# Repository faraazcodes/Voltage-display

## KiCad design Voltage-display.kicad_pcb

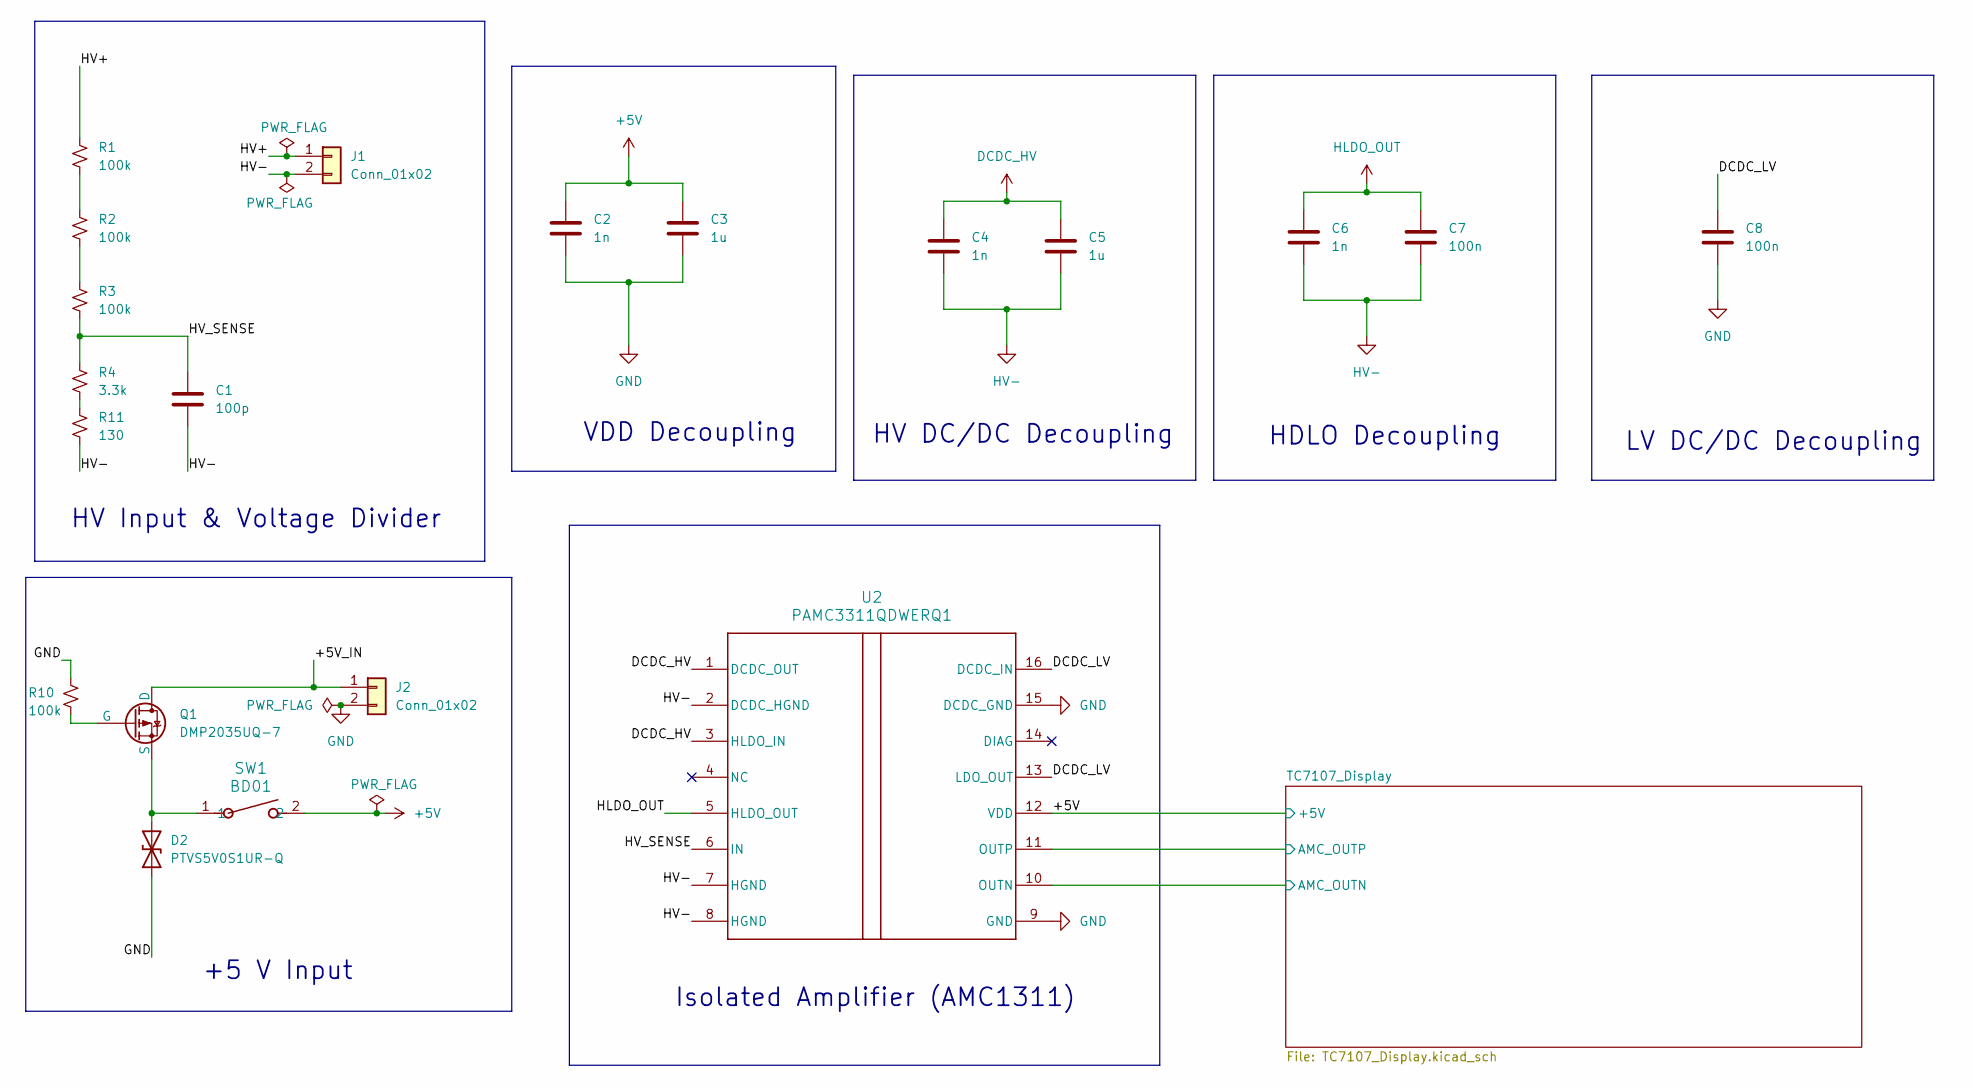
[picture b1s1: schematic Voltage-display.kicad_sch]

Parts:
C1: 100p; C_0805_2012Metric_Pad1.18x1.45mm_HandSolder
C2, C4, C6: 1n; C_0805_2012Metric_Pad1.18x1.45mm_HandSolder
C3, C5: 1u; C_1206_3216Metric_Pad1.33x1.80mm_HandSolder
C7, C8: 100n; C_1206_3216Metric_Pad1.33x1.80mm_HandSolder
D2: PTVS5V0S1UR-Q; SOD123W
J1, J2: Conn_01x02; PinHeader_1x02_P2.54mm_Vertical
Q1: DMP2035UQ-7; SOT96P240X115-3N
R1, R2, R3, R10: 100k; R_1206_3216Metric_Pad1.30x1.75mm_HandSolder
R4: 3.3k; R_1206_3216Metric_Pad1.30x1.75mm_HandSolder
R11: 130; R_1206_3216Metric_Pad1.30x1.75mm_HandSolder
SW1: BD01; SW_BD01_CNK
U2: PAMC3311QDWERQ1; DWE0016A-IPC_A

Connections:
+5V: C2.1, C3.1, SW1.2, U2.12 (VDD); also elsewhere on the board
/+5V_IN: J2.1, Q1.1 (D)
/DCDC_LV: C8.1, U2.13 (LDO_OUT), U2.16 (DCDC_IN)
/HV+: J1.1, R1.1
/HV_SENSE: C1.1, R3.2, R4.1, U2.6 (IN)
/TC7107_Display/AMC_OUTN: U2.10 (OUTN); also elsewhere on the board
/TC7107_Display/AMC_OUTP: U2.11 (OUTP); also elsewhere on the board
DCDC_HV: C4.1, C5.1, U2.1 (DCDC_OUT), U2.3 (HLDO_IN)
GND: C2.2, C3.2, C8.2, D2.1 (A1), J2.2, R10.1, U2.9 (GND), U2.15 (DCDC_GND); also elsewhere on the board
HLDO_OUT: C6.1, C7.1, U2.5 (HLDO_OUT)
HV-: C1.2, C4.2, C5.2, C6.2, C7.2, J1.2, R11.2, U2.2 (DCDC_HGND), U2.7 (HGND), U2.8 (HGND)
unnamed: D2.2 (A2), Q1.3 (S), SW1.1
unnamed: Q1.2 (G), R10.2
unnamed: R1.2, R2.1
unnamed: R2.2, R3.1
unnamed: R4.2, R11.1

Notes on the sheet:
VDD Decoupling
Isolated Amplifier (AMC1311)
+5 V Input
HDLO Decoupling
HV DC/DC Decoupling
HV Input & Voltage Divider
LV DC/DC Decoupling

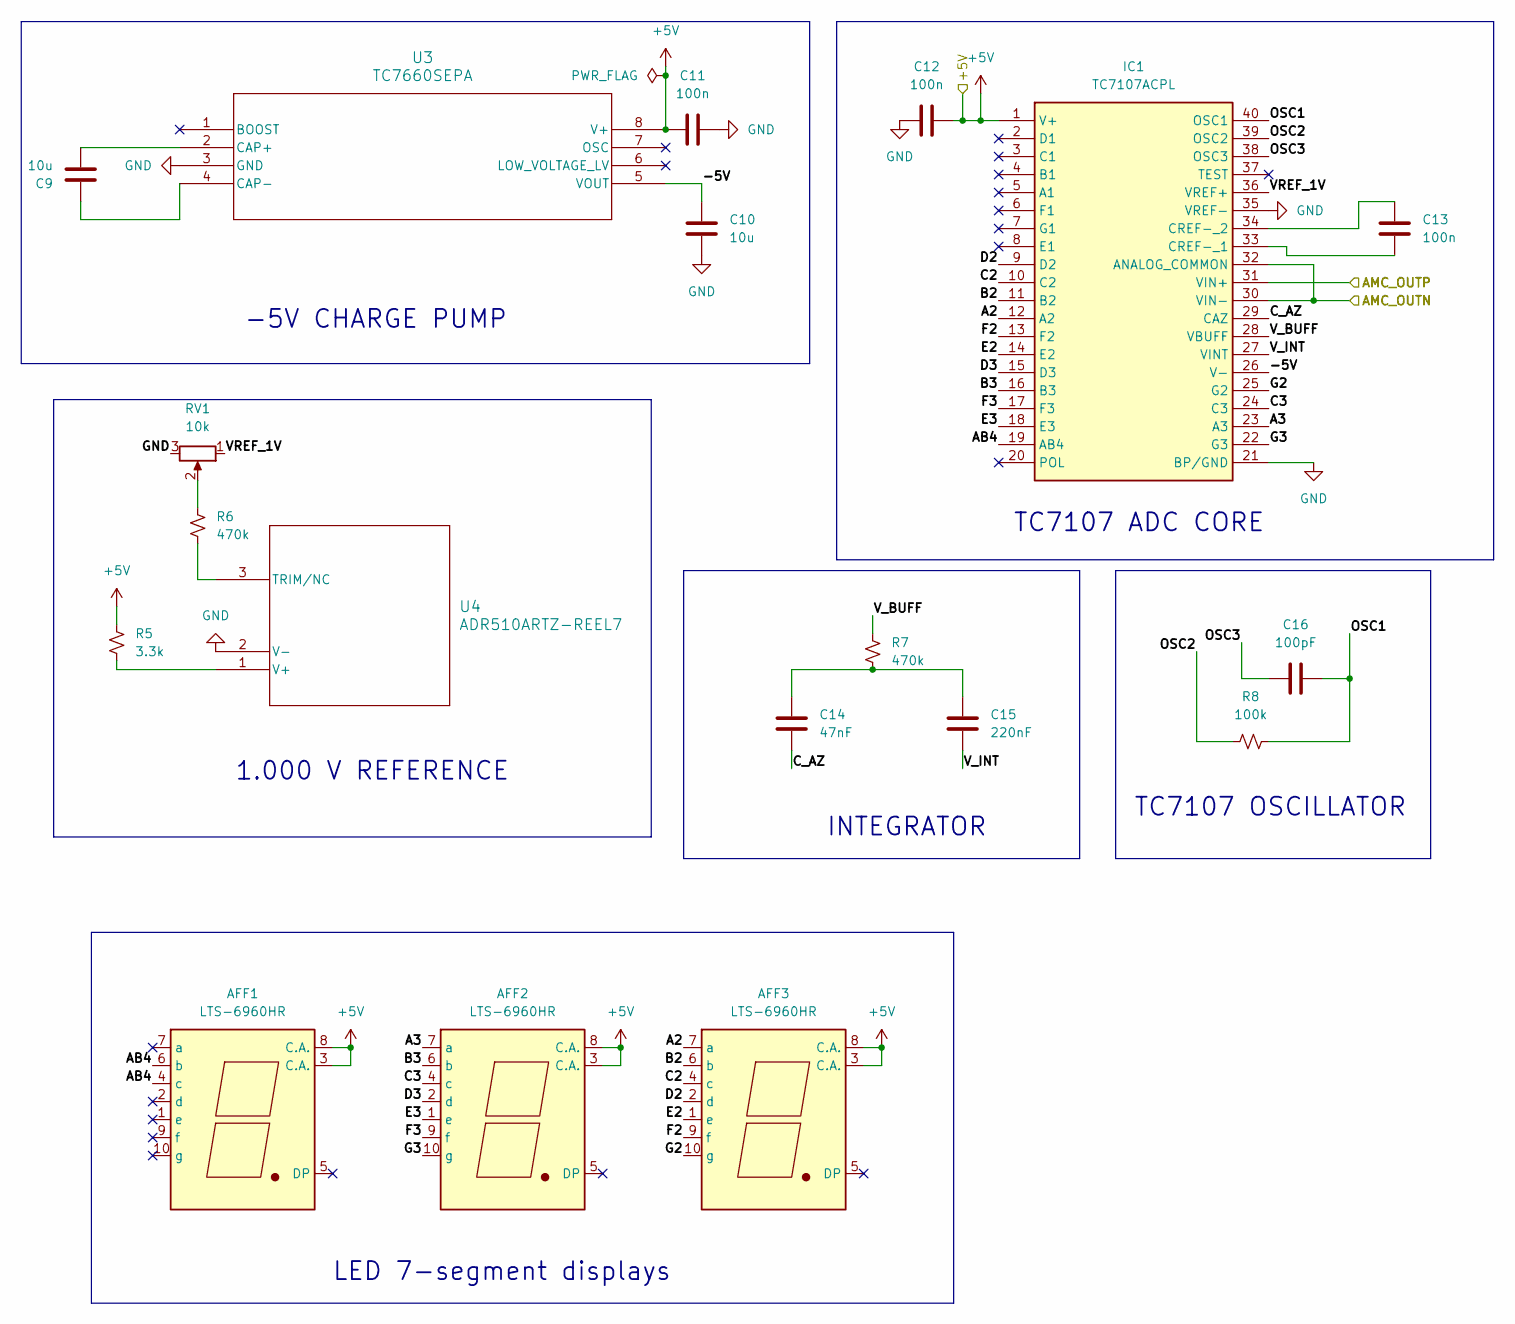
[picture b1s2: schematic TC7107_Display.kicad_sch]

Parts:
AFF1, AFF2, AFF3: LTS-6960HR; 7SegmentLED_LTS6760_LTS6780
C9, C10: 10u; C_1206_3216Metric_Pad1.33x1.80mm_HandSolder
C11, C12: 100n; C_0805_2012Metric_Pad1.18x1.45mm_HandSolder
C13: 100n; C_Rect_L7.2mm_W2.5mm_P5.00mm_FKS2_FKP2_MKS2_MKP2
C14: 47nF; C_Rect_L7.2mm_W2.5mm_P5.00mm_FKS2_FKP2_MKS2_MKP2
C15: 220nF; C_Rect_L7.2mm_W3.0mm_P5.00mm_FKS2_FKP2_MKS2_MKP2
C16: 100pF; C_0805_2012Metric_Pad1.18x1.45mm_HandSolder
IC1: TC7107ACPL; DIP-40_W15.24mm; Mouser Part Number 579-TC7107ACPL
R5: 3.3k; R_0805_2012Metric_Pad1.20x1.40mm_HandSolder
R6, R7: 470k; R_0805_2012Metric_Pad1.20x1.40mm_HandSolder
R8: 100k; R_0805_2012Metric_Pad1.20x1.40mm_HandSolder
RV1: 10k; Potentiometer_Bourns_3296W_Vertical
U3: TC7660SEPA; PDIP8_300MC_MCH
U4: ADR510ARTZ-REEL7; RT_3_ADI

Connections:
+5V: AFF1.3 (C.A.), AFF1.8 (C.A.), AFF2.3 (C.A.), AFF2.8 (C.A.), AFF3.3 (C.A.), AFF3.8 (C.A.), C11.2, C12.1, IC1.1 (V+), R5.1, U3.8 (V+); also elsewhere on the board
/TC7107_Display/-5V: C10.1, IC1.26 (V-), U3.5 (VOUT)
/TC7107_Display/A2: AFF3.7 (a), IC1.12 (A2)
/TC7107_Display/A3: AFF2.7 (a), IC1.23 (A3)
/TC7107_Display/AB4: AFF1.4 (c), AFF1.6 (b), IC1.19 (AB4)
/TC7107_Display/AMC_OUTN: IC1.30 (VIN-), IC1.32 (ANALOG_COMMON); also elsewhere on the board
/TC7107_Display/AMC_OUTP: IC1.31 (VIN+); also elsewhere on the board
/TC7107_Display/B2: AFF3.6 (b), IC1.11 (B2)
/TC7107_Display/B3: AFF2.6 (b), IC1.16 (B3)
/TC7107_Display/C2: AFF3.4 (c), IC1.10 (C2)
/TC7107_Display/C3: AFF2.4 (c), IC1.24 (C3)
/TC7107_Display/C_AZ: C14.2, IC1.29 (CAZ)
/TC7107_Display/D2: AFF3.2 (d), IC1.9 (D2)
/TC7107_Display/D3: AFF2.2 (d), IC1.15 (D3)
/TC7107_Display/E2: AFF3.1 (e), IC1.14 (E2)
/TC7107_Display/E3: AFF2.1 (e), IC1.18 (E3)
/TC7107_Display/F2: AFF3.9 (f), IC1.13 (F2)
/TC7107_Display/F3: AFF2.9 (f), IC1.17 (F3)
/TC7107_Display/G2: AFF3.10 (g), IC1.25 (G2)
/TC7107_Display/G3: AFF2.10 (g), IC1.22 (G3)
/TC7107_Display/OSC1: C16.2, IC1.40 (OSC1), R8.2
/TC7107_Display/OSC2: IC1.39 (OSC2), R8.1
/TC7107_Display/OSC3: C16.1, IC1.38 (OSC3)
/TC7107_Display/VREF_1V: IC1.36 (VREF+), RV1.1
/TC7107_Display/V_BUFF: IC1.28 (VBUFF), R7.1
/TC7107_Display/V_INT: C15.2, IC1.27 (VINT)
GND: C10.2, C11.1, C12.2, IC1.21 (BP/GND), IC1.35 (VREF-), RV1.3, U3.3 (GND), U4.2 (V-); also elsewhere on the board
unnamed: C14.1, C15.1, R7.2
unnamed: C13.2, IC1.33 (CREF-_1)
unnamed: C13.1, IC1.34 (CREF-_2)
unnamed: R6.1, RV1.2
unnamed: C9.2, U3.2 (CAP+)
unnamed: C9.1, U3.4 (CAP-)
unnamed: R6.2, U4.3 (TRIM/NC)
unnamed: R5.2, U4.1 (V+)

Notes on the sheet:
TC7107 ADC CORE
1.000 V REFERENCE
INTEGRATOR
-5V CHARGE PUMP
LED 7-segment displays
TC7107 OSCILLATOR

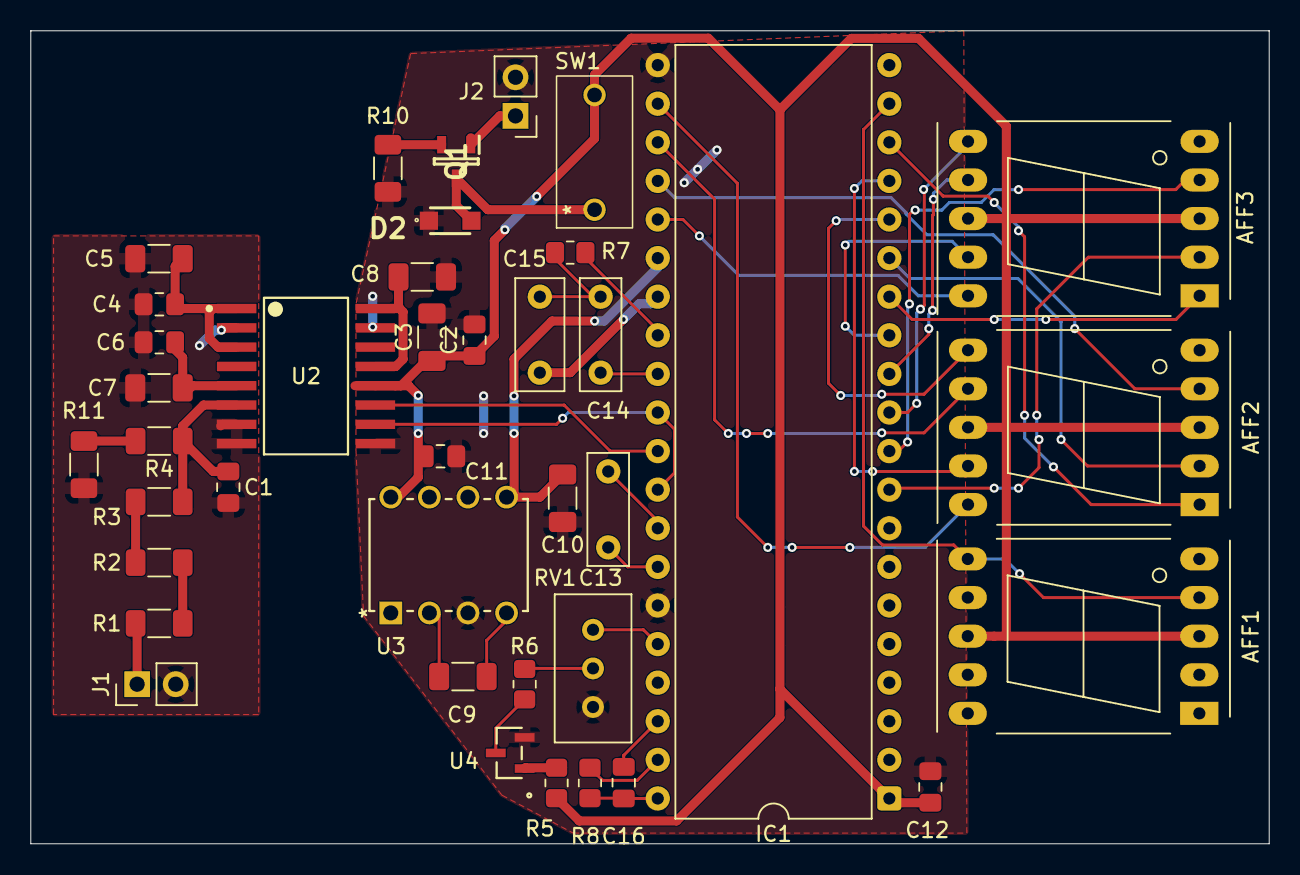
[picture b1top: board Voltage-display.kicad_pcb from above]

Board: 2 copper layers, 81.5 x 53.5 mm, 39 parts (0 on the bottom side), 47 nets.
